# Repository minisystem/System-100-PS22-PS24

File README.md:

Roland System 100 Model 101/102 Power Supply Replacement
============

Replaces Roland part # PS22 (110V) or PS24 (220V). I had a Model 102 come in that was missing its power supply so I designed a replacement. It is a straight clone of the schematic from the Model 102 service manual. The BOM from the service manual can be used directly with the exception of the 2SD234 power transistors (replaced with TIP31A equivalent) and the diode bridges (replaced with individual 1N4003). 

EDA files generated in KiCad 4.0.2. Schematic library here: https://github.com/minisystem/MyKicadLibraries/blob/master/MySynthParts.lib

KiCad GitHub libraries required as well. :/

0.156" MTA header: Molex part # 0009652088
trimmers: Bourns 3362P or equivalent

There are large copper pours top and bottom that were intended to be used as heatsinks, but they are almost certainly inadequate. Use a large external heat sink for each power transistor. The orignal heatsinks will work fine.

Mounting holes match original power supply.

Hardware design by Minisystem: jeff@minisystem.ca 

LICENSE
=======
cc-by-nc-sa
https://creativecommons.org/licenses/by-nc-sa/4.0/

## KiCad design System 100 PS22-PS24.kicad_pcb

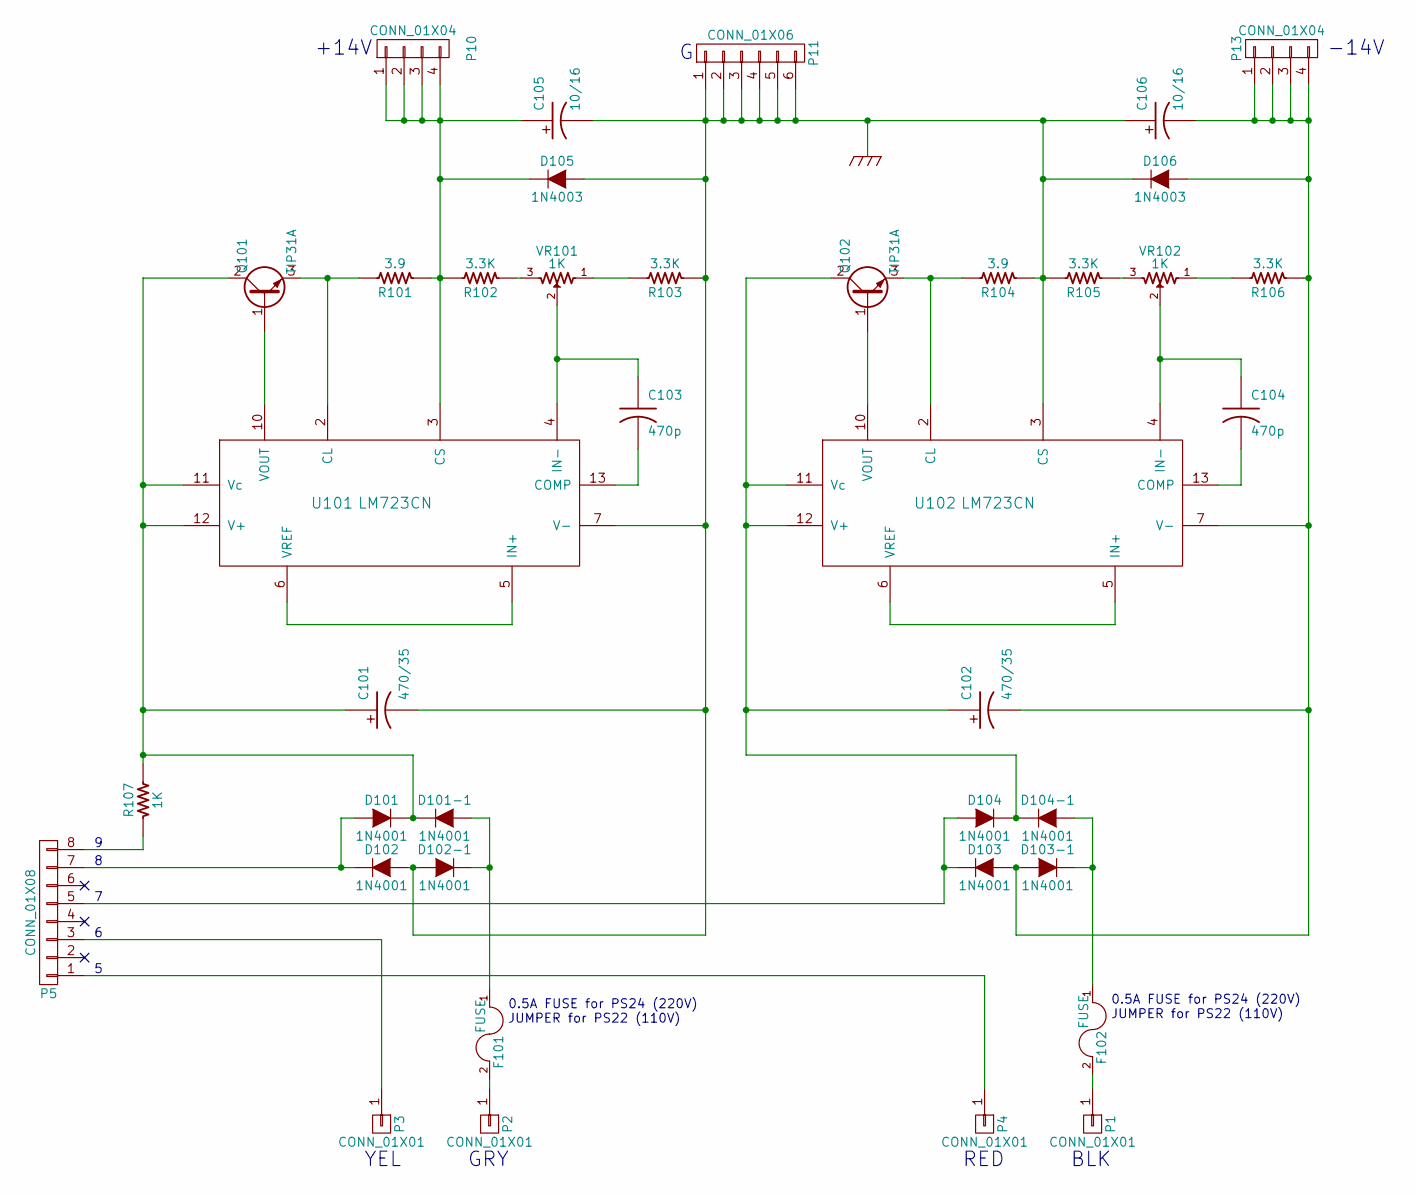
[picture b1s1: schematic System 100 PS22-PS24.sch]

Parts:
C101, C102: 470/35; 5MM-POL-CAP
C103, C104: 470p; C_Disc_D6_P5
C105, C106: 10/16; 2MM-POL-CAP
D101, D101-1, D102, D102-1, D103, D103-1, D104, D104-1: 1N4001; Diode_DO-41_SOD81_Horizontal_RM10
D105, D106: 1N4003; Diode_DO-41_SOD81_Horizontal_RM10
F101, F102: FUSE; Fuseholder5x20_horiz_open_inline_Type-I
P1, P2, P3, P4: CONN_01X01; Pin_Header_Straight_1x01
P5: CONN_01X08; kk156_26-60-4080
P10, P13: CONN_01X04; Pin_Header_Straight_1x04
P11: CONN_01X06; Pin_Header_Straight_2x03
Q101, Q102: TIP31A; TO-220_Neutral123_Horizontal_LargePads
R101, R104: 3.9; Resistor_Horizontal_RM10mm
R102, R103, R105, R106: 3.3K; Resistor_Horizontal_RM10mm
R107: 1K; Resistor_Horizontal_RM10mm
U101, U102: LM723CN; DIP-14_W7.62mm
VR101, VR102: 1K; Bourns_3362P

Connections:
GND: C101.2 (-), C105.2 (-), C106.1 (+), D102.2 (A), D102-1.2 (A), D105.2 (A), D106.1 (K), P11.1, P11.2, P11.3, P11.4, P11.5, P11.6, R103.1, R104.1, R105.2, U101.7 (V-), U102.3 (CS)
unnamed: C101.1 (+), D101.1 (K), D101-1.1 (K), Q101.2 (C), R107.2, U101.11 (Vc), U101.12 (V+)
unnamed: C102.1 (+), D104.1 (K), D104-1.1 (K), Q102.2 (C), U102.11 (Vc), U102.12 (V+)
unnamed: C102.2 (-), C106.2 (-), D103.2 (A), D103-1.2 (A), D106.2 (A), P13.1, P13.2, P13.3, P13.4, R106.1, U102.7 (V-)
unnamed: C103.1, U101.4 (IN-), VR101.2
unnamed: C103.2, U101.13 (COMP)
unnamed: C104.1, U102.4 (IN-), VR102.2
unnamed: C104.2, U102.13 (COMP)
unnamed: C105.1 (+), D105.1 (K), P10.1, P10.2, P10.3, P10.4, R101.1, R102.2, U101.3 (CS)
unnamed: D101-1.2 (A), D102-1.1 (K), F101.1
unnamed: D101.2 (A), D102.1 (K), P5.7
unnamed: D103-1.1 (K), D104-1.2 (A), F102.1
unnamed: D103.1 (K), D104.2 (A), P5.5
unnamed: F101.2, P2.1
unnamed: F102.2, P1.1
unnamed: P3.1, P5.3
unnamed: P4.1, P5.1
unnamed: P5.8, R107.1
unnamed: Q101.1 (B), U101.10 (VOUT)
unnamed: Q101.3 (E), R101.2, U101.2 (CL)
unnamed: Q102.1 (B), U102.10 (VOUT)
unnamed: Q102.3 (E), R104.2, U102.2 (CL)
unnamed: R102.1, VR101.3
unnamed: R103.2, VR101.1
unnamed: R105.1, VR102.3
unnamed: R106.2, VR102.1
unnamed: U101.5 (IN+), U101.6 (VREF)
unnamed: U102.5 (IN+), U102.6 (VREF)

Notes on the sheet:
+14V
-14V
0.5A FUSE for PS24 (220V) JUMPER for PS22 (110V)
YEL
GRY
RED
BLK

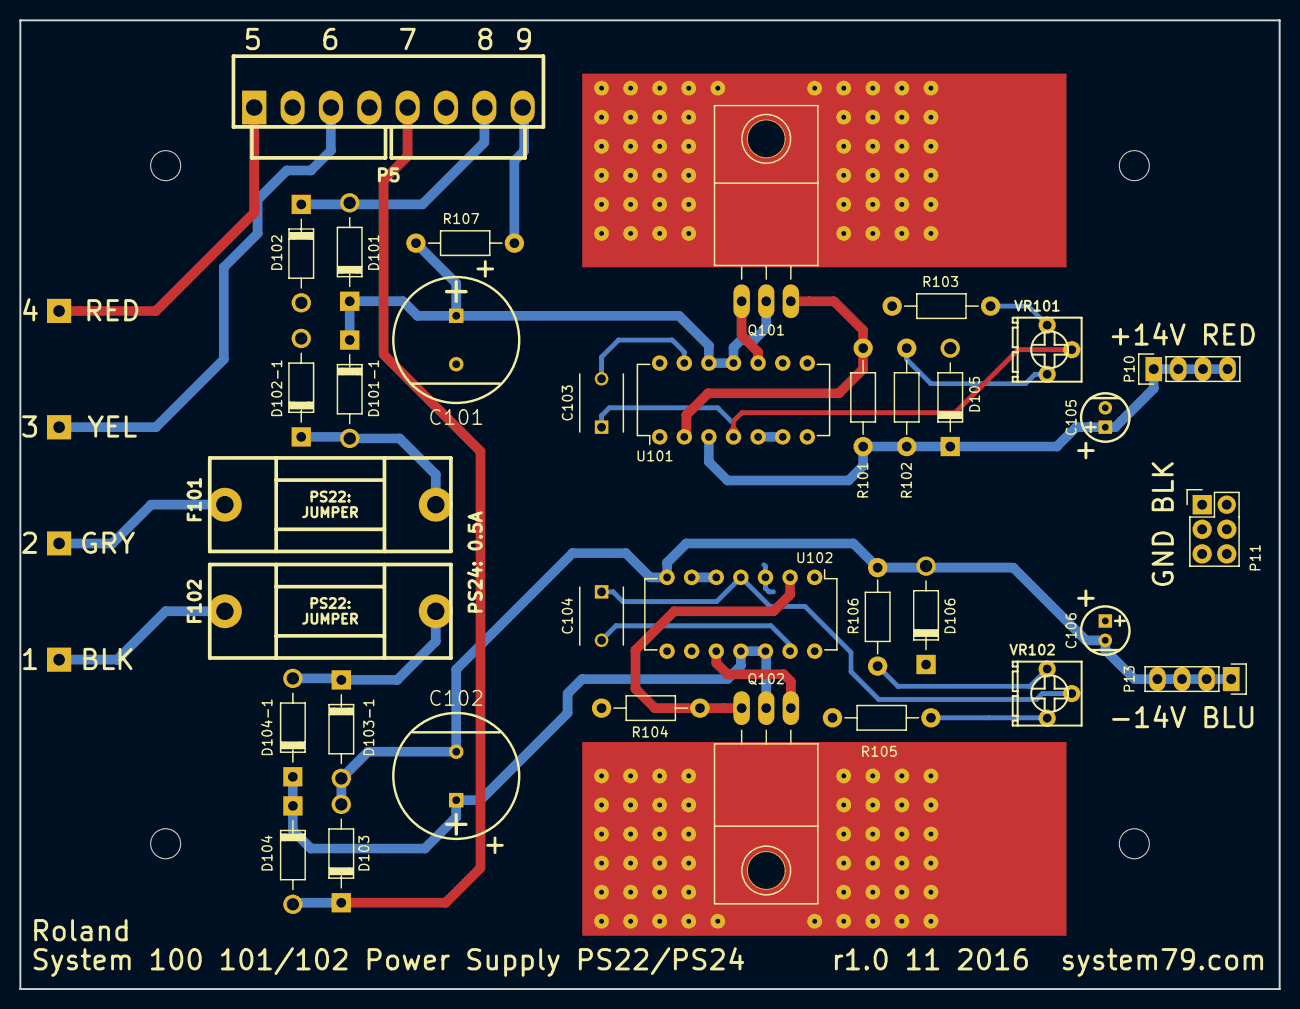
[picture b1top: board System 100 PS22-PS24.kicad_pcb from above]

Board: 2 copper layers, 130.0 x 100.0 mm, 43 parts (0 on the bottom side), 28 nets.

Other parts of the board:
HOLE-M3, HOLE-M3#2, HOLE-M3#3, HOLE-M3#4: VAL**; HOLE-M3

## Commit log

2016-11-13 footprints assigned
2016-11-14 routed
2016-11-14 gerbers generated, ready to order
